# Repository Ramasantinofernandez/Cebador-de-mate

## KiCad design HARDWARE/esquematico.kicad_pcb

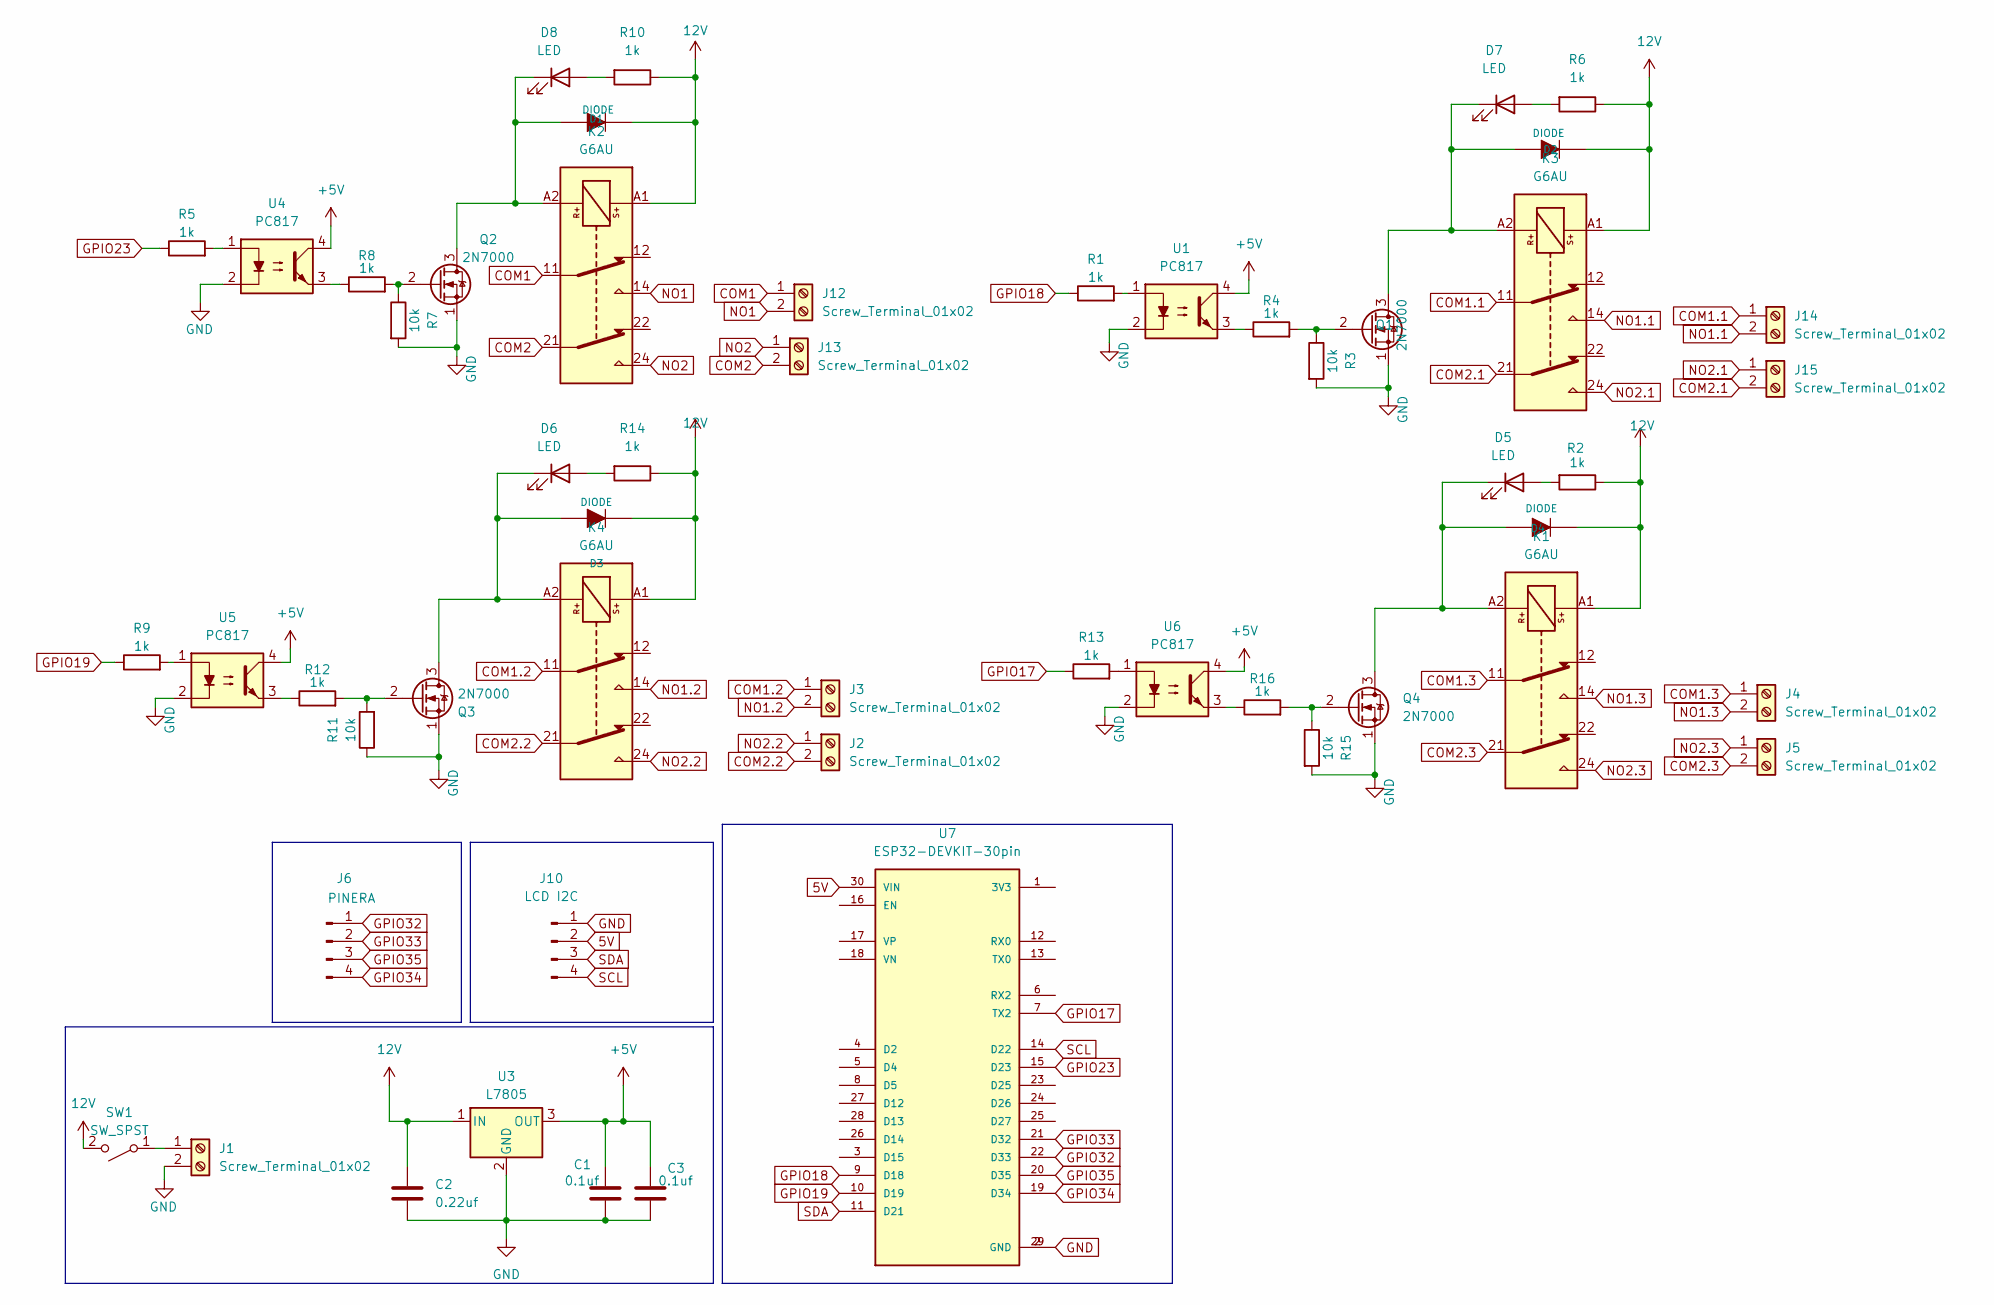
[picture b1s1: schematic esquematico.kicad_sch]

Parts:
C1: 0.1uf; C_0805_2012Metric_Pad1.18x1.45mm_HandSolder
C2: 0.22uf; C_0805_2012Metric_Pad1.18x1.45mm_HandSolder
C3: 0.1uf; CP_Radial_D8.0mm_P5.00mm
D1, D2, D3, D4: DIODE; D_SMA
D5, D6, D7, D8: LED; LED_D5.0mm
J1, J2, J3, J4, J5, J12, J13, J14, J15: Screw_Terminal_01x02; TerminalBlock_bornier-2_P5.08mm
J6: PINERA; PinHeader_1x04_P2.54mm_Vertical
J10: LCD I2C; pin_strip_4
K1, K2, K3, K4: G6AU; Relay_DPDT_Omron_G6A
Q1, Q2, Q3, Q4: 2N7000; to92
R1, R2, R4, R5, R6, R8, R9, R10, R12, R13, R14, R16: 1k; R_0805_2012Metric
R3, R7, R11, R15: 10k; R_0805_2012Metric
SW1: SW_SPST; PinHeader_1x02_P2.54mm_Vertical
U1, U4, U5, U6: PC817; SSO-4_6.7x5.1mm_P2.54mm_Clearance8mm
U3: L7805; TO-263-3_TabPin2
U7: ESP32-DEVKIT-30pin; MODULE_ESP32_DEVKIT_V1; PARTREV N/A

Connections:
5V: J10.2, U7.30 (VIN)
12V: C2.1, D1.2 (K), D2.2 (K), D3.2 (K), D4.2 (K), K1.A1, K2.A1, K3.A1, K4.A1, R2.1, R6.1, R10.1, R14.1, SW1.2 (B), U3.1 (IN)
+5V: C1.1, C3.1, U1.4, U3.3 (OUT), U4.4, U5.4, U6.4
COM1: J12.1, K2.11
COM1.1: J14.1, K3.11
COM1.2: J3.1, K4.11
COM1.3: J4.1, K1.11
COM2: J13.2, K2.21
COM2.1: J15.2, K3.21
COM2.2: J2.2, K4.21
COM2.3: J5.2, K1.21
GND: C1.2, C2.2, C3.2, J1.2, J10.1, Q1.1 (S), Q2.1 (S), Q3.1 (S), Q4.1 (S), R3.2, R7.2, R11.1, R15.2, U1.2, U3.2 (GND), U4.2, U5.2, U6.2, U7.2 (GND), U7.29 (GND)
GPIO17: R13.1, U7.7 (TX2)
GPIO18: R1.1, U7.9 (D18)
GPIO19: R9.1, U7.10 (D19)
GPIO23: R5.1, U7.15 (D23)
GPIO32: J6.1, U7.22 (D33)
GPIO33: J6.2, U7.21 (D32)
GPIO34: J6.4, U7.19 (D34)
GPIO35: J6.3, U7.20 (D35)
NO1: J12.2, K2.14
NO1.1: J14.2, K3.14
NO1.2: J3.2, K4.14
NO1.3: J4.2, K1.14
NO2: J13.1, K2.24
NO2.1: J15.1, K3.24
NO2.2: J2.1, K4.24
NO2.3: J5.1, K1.24
unnamed: D1.1 (A), D8.1 (K), K2.A2, Q2.3 (D)
unnamed: D2.1 (A), D7.1 (K), K3.A2, Q1.3 (D)
unnamed: D3.1 (A), D6.1 (K), K4.A2, Q3.3 (D)
unnamed: D4.1 (A), D5.1 (K), K1.A2, Q4.3 (D)
unnamed: D5.2 (A), R2.2
unnamed: D6.2 (A), R14.2
unnamed: D7.2 (A), R6.2
unnamed: D8.2 (A), R10.2
unnamed: J1.1, SW1.1 (A)
unnamed: Q1.2 (G), R3.1, R4.2
unnamed: Q2.2 (G), R7.1, R8.2
unnamed: Q3.2 (G), R11.2, R12.2
unnamed: Q4.2 (G), R15.1, R16.2
unnamed: R1.2, U1.1
unnamed: R4.1, U1.3
unnamed: R5.2, U4.1
unnamed: R8.1, U4.3
unnamed: R9.2, U5.1
unnamed: R12.1, U5.3
unnamed: R13.2, U6.1
unnamed: R16.1, U6.3
SCL: J10.4, U7.14 (D22)
SDA: J10.3, U7.11 (D21)

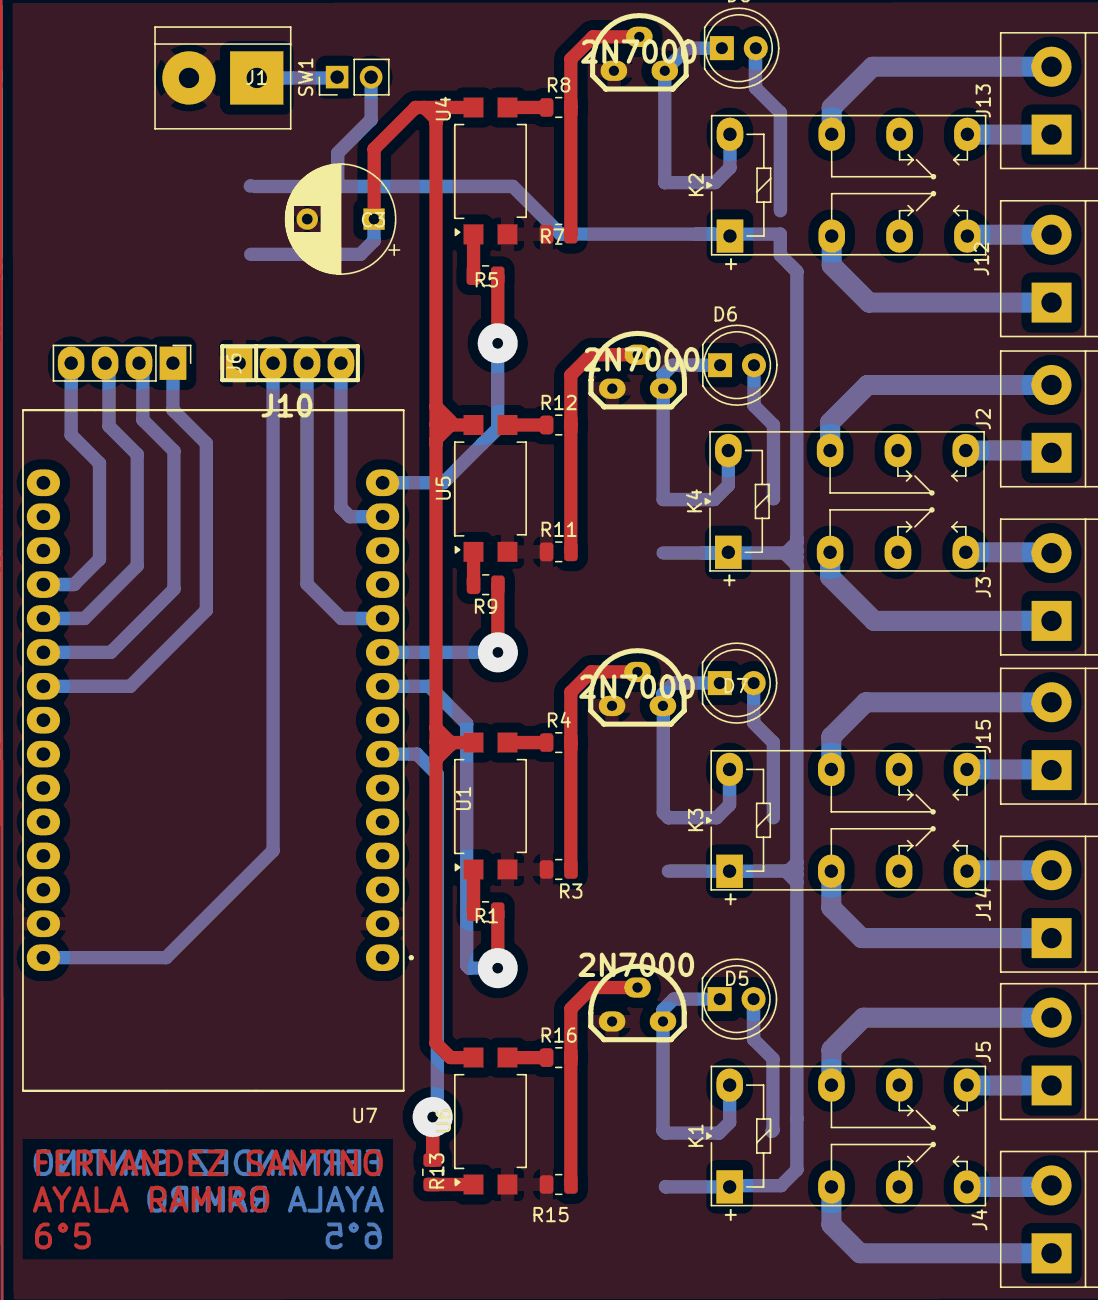
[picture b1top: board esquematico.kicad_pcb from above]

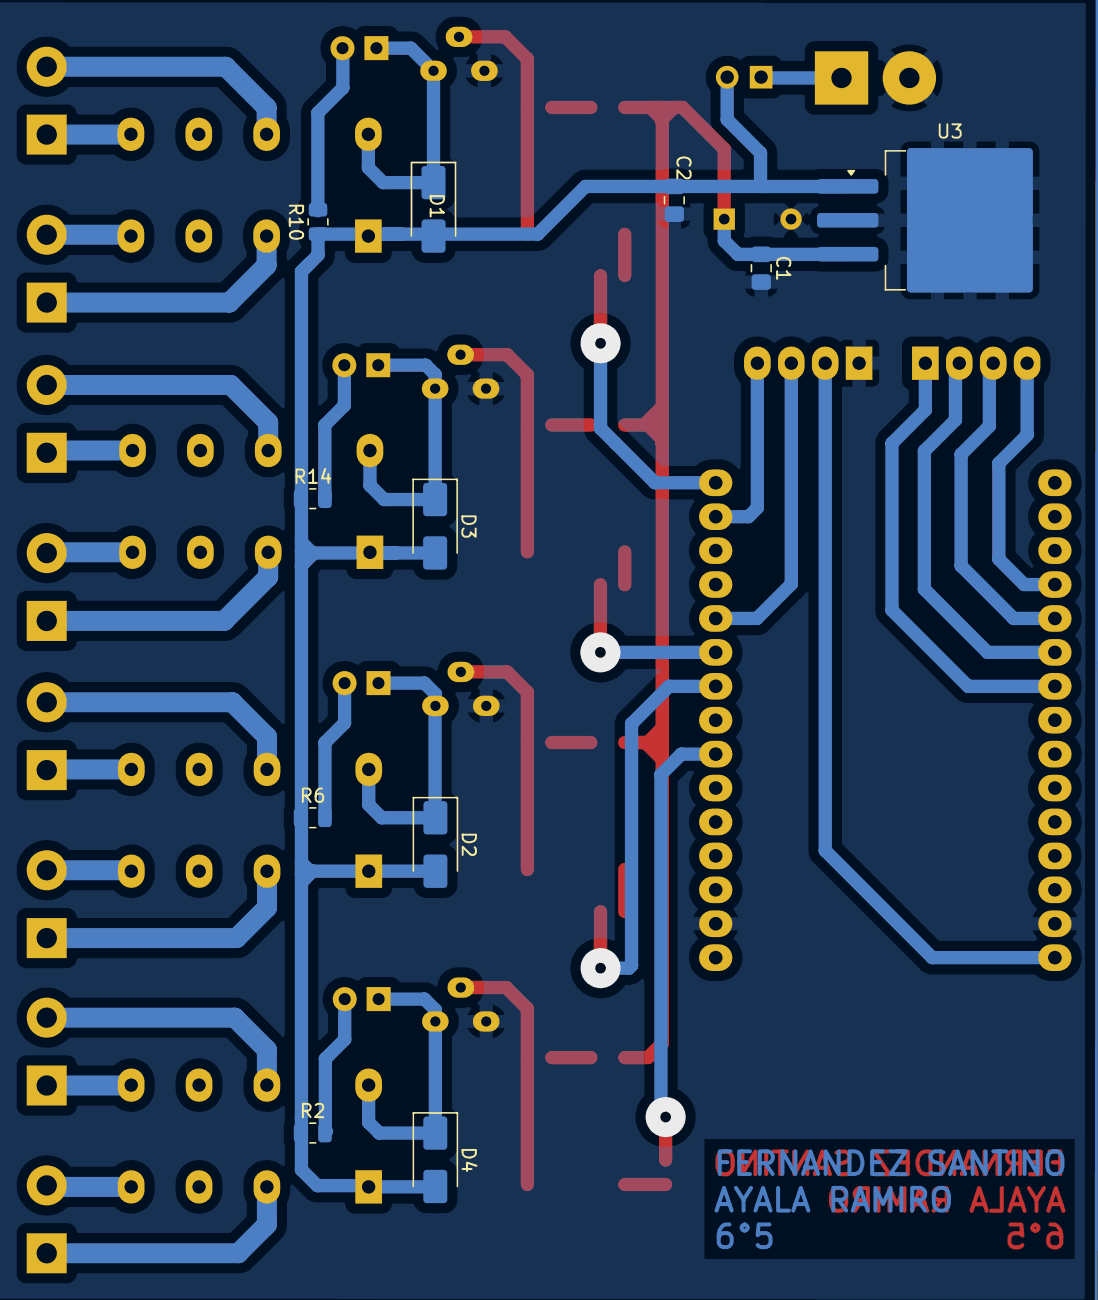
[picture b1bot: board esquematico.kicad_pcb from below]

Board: 2 copper layers, 53 parts (11 on the bottom side), 51 nets.

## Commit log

2025-06-17 placa terminada
2025-06-18 terminamos la placa
2025-06-19 termine de corregir la placa
2025-06-25 agrego otra rama por si al final usamos el otro rele(negro)
2025-06-25 cambie el esp32 de 38 pines por uno de 30
2025-09-28 agregamos el modelo 3d del proyecto y su codigo
